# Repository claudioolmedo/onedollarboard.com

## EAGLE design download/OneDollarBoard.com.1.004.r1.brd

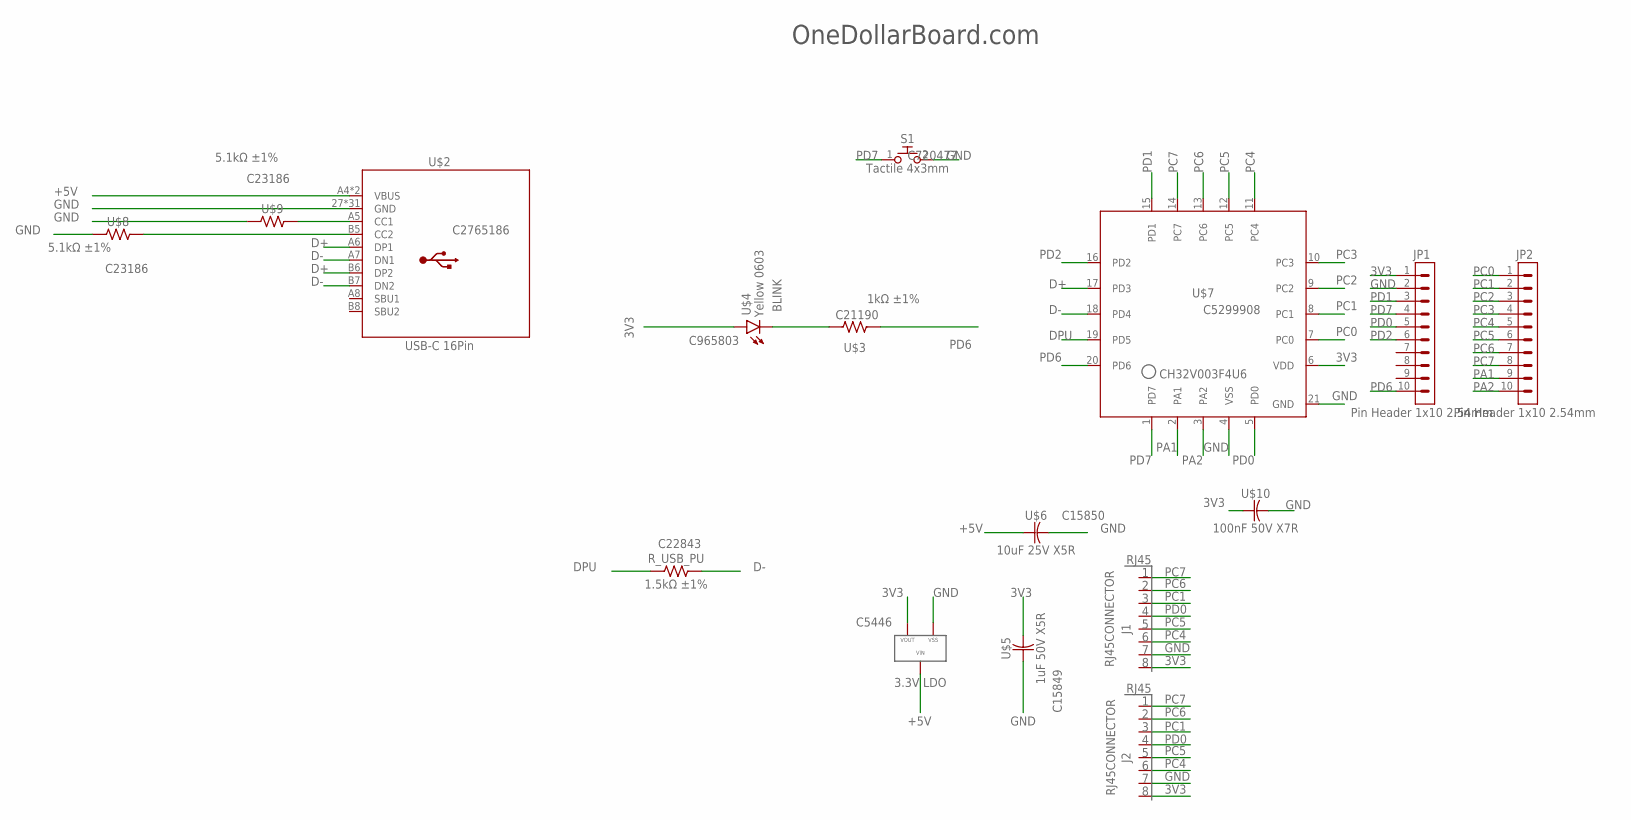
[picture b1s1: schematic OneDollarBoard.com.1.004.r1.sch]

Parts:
J1, J2: RJ45CONNECTOR; 2.54/1.0
JP1, JP2: Pin Header 1x10 2.54mm; 1X10; LCSC C350306
R_USB_PU: 1.5kΩ ±1%; WRIS-RSKS_0603_WAVE; LCSC C22843
S1: Tactile 4x3mm; B3U-1000P(M); LCSC C720477
U$1: 3.3V LDO; XC6206P332MR-G; LCSC C5446
U$2: USB-C 16Pin; CONN_TYPE-C-16P; LCSC C2765186
U$3: 1kΩ ±1%; RESC2208X45; LCSC C21190
U$4: Yellow 0603; LEDC1507X40; LCSC C965803
U$5: 1uF 50V X5R; CPA1UF; LCSC C15849
U$6: 10uF 25V X5R; CAP0603; LCSC C15850
U$7: CH32V003F4U6; LCSC C5299908
U$8, U$9: 5.1kΩ ±1%; WRIS-RSKS_0603_REFLOW; LCSC C23186
U$10: 100nF 50V X7R; CAP0603

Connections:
3V3: J1.P$1 (P1), J2.P$1 (P1), JP1.1, U$1.2, U$4.A, U$5.2, U$7.6 (VDD), U$10.1
+5V: U$1.3, U$2.A4 (VBUS), U$2.B4 (VBUS), U$6.1
BLINK: U$3.1, U$4.C
D+: U$2.A6 (DP1), U$2.B6 (DP2), U$7.17 (PD3)
D-: R_USB_PU.2, U$2.A7 (DN1), U$2.B7 (DN2), U$7.18 (PD4)
DPU: R_USB_PU.1, U$7.19 (PD5)
GND: J1.P$2 (P2), J2.P$2 (P2), JP1.2, S1.2, U$1.1, U$2.27 (GND), U$2.28 (GND), U$2.29 (GND), U$2.30 (GND), U$2.A1 (GND), U$2.B1 (GND), U$2.S_1 (GND), U$2.S_1_H1 (GND), U$2.S_1_H2 (GND), U$2.S_2 (GND), U$2.S_2_H1 (GND), U$2.S_2_H2 (GND), U$2.S_2_H3 (GND), U$2.S_2_H4 (GND), U$2.S_2_H5 (GND), U$2.S_2_H6 (GND), U$2.S_2_H7 (GND), U$2.S_2_H12 (GND), U$2.S_2_H13 (GND), U$2.S_3 (GND), U$2.S_3_H1 (GND), U$2.S_3_H2 (GND), U$2.S_3_H3 (GND), U$2.S_3_H4 (GND), U$2.S_3_H5 (GND), U$2.S_4 (GND), U$2.S_4_H1 (GND), U$2.S_4_H2 (GND), U$2.S_4_H3 (GND), U$2.S_4_H4 (GND), U$2.S_4_H5 (GND), U$5.1, U$6.2, U$7.4 (VSS), U$7.21 (GND), U$8.1, U$9.1, U$10.2
unnamed: U$2.A5 (CC1), U$9.2
unnamed: U$2.B5 (CC2), U$8.2
PA1: JP2.9, U$7.2 (PA1)
PA2: JP2.10, U$7.3 (PA2)
PC0: JP2.1, U$7.7 (PC0)
PC1: J1.P$6 (P6), J2.P$6 (P6), JP2.2, U$7.8 (PC1)
PC2: JP2.3, U$7.9 (PC2)
PC3: JP2.4, U$7.10 (PC3)
PC4: J1.P$3 (P3), J2.P$3 (P3), JP2.5, U$7.11 (PC4)
PC5: J1.P$4 (P4), J2.P$4 (P4), JP2.6, U$7.12 (PC5)
PC6: J1.P$7 (P7), J2.P$7 (P7), JP2.7, U$7.13 (PC6)
PC7: J1.P$8 (P8), J2.P$8 (P8), JP2.8, U$7.14 (PC7)
PD0: J1.P$5 (P5), J2.P$5 (P5), JP1.5, U$7.5 (PD0)
PD1: JP1.3, U$7.15 (PD1)
PD2: JP1.6, U$7.16 (PD2)
PD6: JP1.10, U$3.2, U$7.20 (PD6)
PD7: JP1.4, S1.1, U$7.1 (PD7)

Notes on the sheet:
OneDollarBoard.com

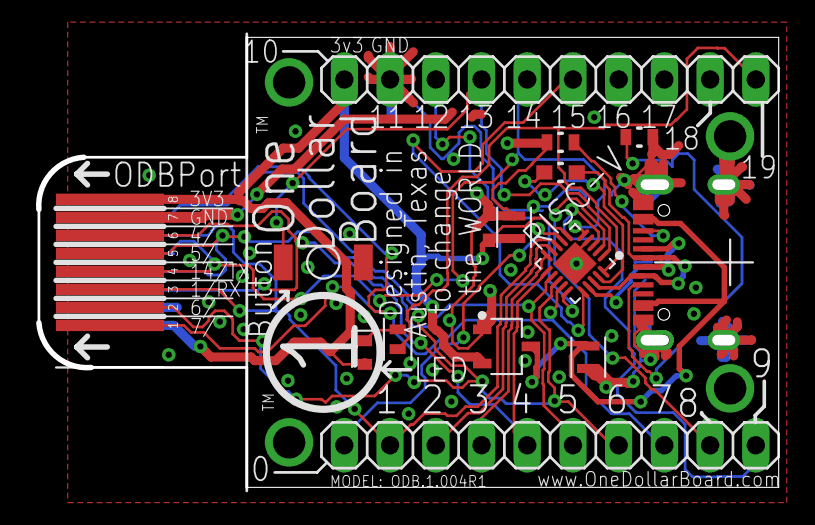
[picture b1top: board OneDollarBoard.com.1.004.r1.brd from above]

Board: 2 copper layers, 40.7 x 24.6 mm, 16 parts (1 on the bottom side), 24 nets.

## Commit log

2026-02-11 Pinout
2026-02-11 Release 1.004 R1
2026-02-11 BOM & Library
2026-02-11 picture
2026-02-11 jlcpcb pcb gerber file
2026-02-11 ready files
2026-02-11 add bom for lcsc
2026-02-11 guide jlpcpcb
2026-02-11 fixed link guides jlcpcb
2026-02-11 fixed J1 and J2 PCB part
2026-02-11 update foundational
2026-02-12 update link
2026-03-13 Add One Dollar Board pinout YAML
    Add docs/onedollarboard.1.004.r1.pinout.yaml containing pinout documentation for One Dollar Board v1.004 R1. The YAML lists the MCU (CH32V003F4U6), connector (ODB/RJ45) and per-pin mappings (signals,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
2026-03-13 Add OneDollarBoard v1.004.r1 pinout SVGs
    Add documentation assets: docs/OneDollarBoard.com.v1.004.r1.pinout.svg and the corresponding AI source/docs file docs/OneDollarBoard.com.v1.004.r1.pinout_ai_doc.svg. These Inkscape-generated vector f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
2026-03-18 Add OneDollarBoard.com v1.004 STL
    Add the binary STL 3D model (download/OneDollarBoard.com.1.004.stl) for OneDollarBoard.com version 1.004 to the repository's download folder to provide a printable model(mecanical) for users.
